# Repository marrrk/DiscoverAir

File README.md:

# DiscoverAir

A Datalogging HAT for the STM32F0 Discovery Board

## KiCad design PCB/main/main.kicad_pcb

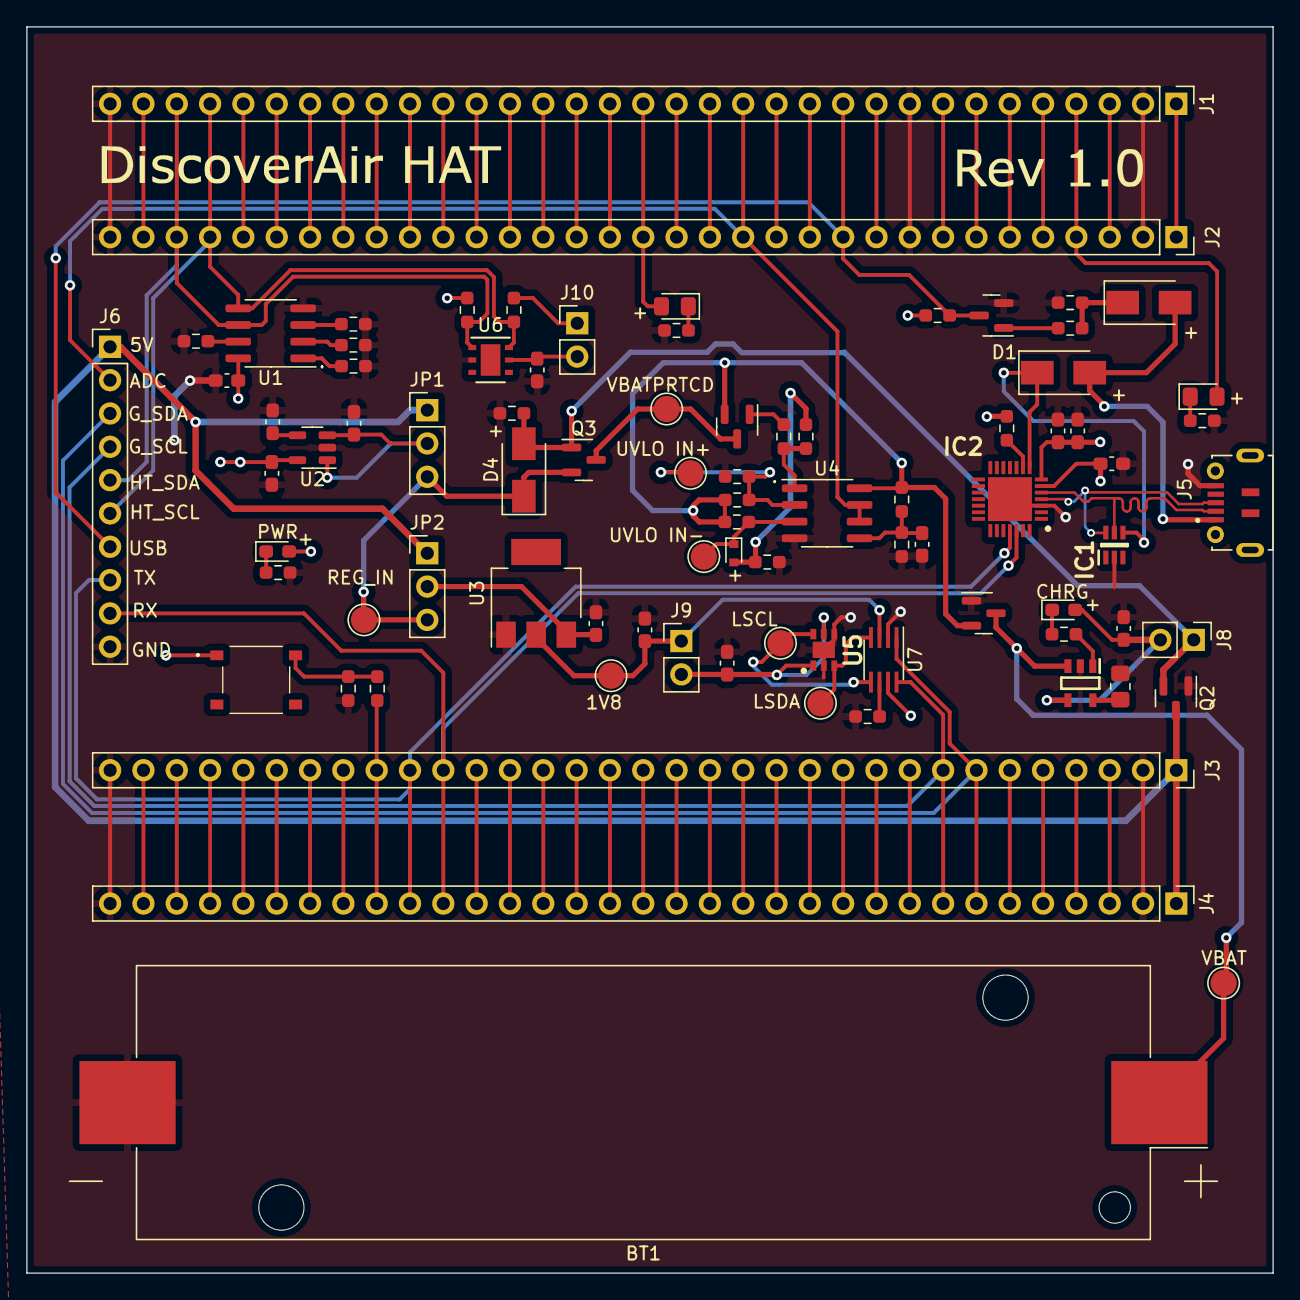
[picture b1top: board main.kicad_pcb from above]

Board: 2 copper layers, 95.0 x 95.0 mm, 84 parts (0 on the bottom side), 101 nets.

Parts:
BT1: Battery_Cell; BatteryHolder_Keystone_1042_1x18650
C1, C5, C6, C8, C9, C10, C11: 1uF; C_0603_1608Metric_Pad1.08x0.95mm_HandSolder
C2, C3, C4, C12, C13: 100nF; C_0603_1608Metric_Pad1.08x0.95mm_HandSolder
C7: 10nF; C_0603_1608Metric_Pad1.08x0.95mm_HandSolder
D1, D2, D4: D_Schottky; D_SMA
D3: CHRG; LED_0603_1608Metric_Pad1.05x0.95mm_HandSolder
D5: D_Zener; D_SOD-523
D6: PWR; LED_0603_1608Metric_Pad1.05x0.95mm_HandSolder
D7, D8: USER; LED_0805_2012Metric_Pad1.15x1.40mm_HandSolder
IC1: SMF05CT1G; SOT65P210X110-6N
IC2: CP2102-GMR; QFN50P500X500X100-29N-D
IC3: TP4054-42-SOT25-R; SOT95P280X100-5N
J1, J4: Conn_01x33_Female; PinHeader_1x33_P2.54mm_Vertical
J2, J3: Conn_01x33_Female; PinSocket_1x33_P2.54mm_Vertical
J5: USB_B_Micro; SHOUHAN_MICROXNJ
J6: Conn_01x10_Male; PinHeader_1x10_P2.54mm_Vertical
J8, J9, J10: Conn_01x02_Male; PinHeader_1x02_P2.54mm_Vertical
JP1, JP2: Jumper_3_Open; PinHeader_1x03_P2.54mm_Vertical
Q1: Q_NMOS_GSD; SOT-23
Q2, Q3, Q4, Q5: Q_PMOS_GSD; SOT-23
R1, R2, R3, R4, R5, R6, R7, R8, R10, R20, R22, R23: 4k7; R_0603_1608Metric_Pad0.98x0.95mm_HandSolder
R9: 510; R_0603_1608Metric_Pad0.98x0.95mm_HandSolder
R11: 5K1; R_0805_2012Metric_Pad1.20x1.40mm_HandSolder
R12, R19: 2.2M; R_0603_1608Metric_Pad0.98x0.95mm_HandSolder
R13, R15, R18: 1M; R_0603_1608Metric_Pad0.98x0.95mm_HandSolder
R14, R26: 300K; R_0603_1608Metric_Pad0.98x0.95mm_HandSolder
R16, R21, R24, R25, R27: 150; R_0603_1608Metric_Pad0.98x0.95mm_HandSolder
R17: 100; R_0603_1608Metric_Pad0.98x0.95mm_HandSolder
S1: TS-1187A-B-A-B; TS1187ABAB
TP2: 1V8; TestPoint_Pad_D2.0mm
TP4: UVLO_Out; TestPoint_Pad_D2.0mm
TP5: REG_IN; TestPoint_Pad_D2.0mm
TP6: VBAT; TestPoint_Pad_D2.0mm
TP7: UVLO V+; TestPoint_Pad_D2.0mm
TP8: UVLO V-; TestPoint_Pad_D2.0mm
TP9: GAS_SDA; TestPoint_Pad_D2.0mm
TP10: GAS_SCL; TestPoint_Pad_D2.0mm
U1: CAT24C256; SOIC-8_3.9x4.9mm_P1.27mm
U2: SGM2007-3.3XN5/TR; SOT-23-5
U3: AMS1117-1.8; SOT-223
U4: LM358; SOIC-8_3.9x4.9mm_P1.27mm
U5: SGP30-2.5k; SON80P245X245X90-7N
U6: HDC1080; Texas_PWSON-N6
U7: TXS0102DCT; SSOP-8_2.95x2.8mm_P0.65mm

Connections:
+1V8: C8.1, J9.1, TP2.1, U3.2 (VO), U7.3 (VCCA)
+3V0: C1.1, C2.1, C3.1, C4.1, C9.1, D6.2 (A), IC2.6 (VDD), IC2.7 (REGIN), J1.1, J2.1, J10.1, R3.1, R4.2, R22.2, R23.2, S1.A1 (COM_1), U1.8 (VCC), U2.5 (OUT), U7.7 (VCCB)
+5V: J3.1, J4.1, J6.1, JP1.1 (A), JP2.1 (A), Q2.3 (D)
/BOOT: J3.6, J4.6
/DN: IC1.5 (K_4), IC2.5 (D-), J5.2 (D-)
/DP: IC1.6 (K_5), IC2.4 (D+), J5.3 (D+)
/NRST: J1.10, J2.10
/PA0: J1.15, J2.15
/PA1: J1.16, J2.16
/PA2: D7.2 (A), J1.17, J2.17
/PA3: J1.18, J2.18
/PA4: J1.21, J2.21
/PA5: J1.22, J2.22
/PA6: J1.23, J2.23
/PA7: J1.24, J2.24
/PA8: J3.25, J4.25, R27.2
/PA9: IC2.25 (RXD), J3.24, J4.24, J6.8
/PA10: IC2.26 (TXD), J3.23, J4.23, J6.9
/PA11: J3.22, J4.22
/PA12: J3.21, J4.21
/PA13: J3.20, J4.20
/PA14: J3.17, J4.17
/PA15: J3.16, J4.16
/PB0: J1.27, J2.27
/PB1: J1.28, J2.28
/PB2: J1.29, J2.29
/PB3: J3.11, J4.11
/PB4: J3.10, J4.10
/PB5: J3.9, J4.9
/PB6: J3.8, J4.8, J6.4, U7.8 (B1)
/PB7: J3.7, J4.7, J6.3, U7.1 (B2)
/PB8: J3.4, J4.4
/PB9: J3.3, J4.3
/PB10: J1.30, J2.30, J6.6, R22.1, U1.5 (SDA), U6.6 (SCL)
/PB11: J1.31, J2.31, J6.5, R23.1, U1.6 (SCL), U6.1 (SDA)
/PB12: J1.32, J2.32
/PB13: J3.32, J4.32
/PB14: J3.31, J4.31
/PB15: J3.30, J4.30
/PC0: J1.11, J2.11, J6.7, Q1.3 (D), R3.2
/PC1: J1.12, J2.12
/PC2: J1.13, J2.13
/PC3: J1.14, J2.14, J6.2, U4.6 (-), U4.7
/PC4: J1.25, J2.25
/PC5: J1.26, J2.26
/PC6: J3.29, J4.29
/PC7: J3.28, J4.28
/PC8: J3.27, J4.27
/PC9: J3.26, J4.26
/PC10: J3.15, J4.15
/PC11: J3.14, J4.14
/PC12: J3.13, J4.13
/PC13: D8.2 (A), J1.4, J2.4
/PC14: J1.5, J2.5
/PC15: J1.6, J2.6
/PD2: J3.12, J4.12
/PF0: J1.7, J2.7
/PF1: J1.8, J2.8
/PF4: J1.19, J2.19
/PF5: J1.20, J2.20
/PF6: J3.19, J4.19
/PF7: J3.18, J4.18
/Power/Charger_In: D4.2 (A), J8.1, Q2.2 (S), Q3.1 (G), R10.2
/Power/REG_IN: D4.1 (K), JP1.3 (B), JP2.3 (B), Q3.2 (S), TP5.1
/Power/UVLO_IN: Q4.2 (S), Q5.2 (S), R12.1, R14.1, R16.1, U4.8 (V+)
/Power/VBAT: BT1.1 (+), IC3.3 (BAT), Q4.3 (D), TP6.1
/Power/VBAT_PRTCD: Q3.3 (D), Q5.3 (D), TP4.1
/VBAT: J1.3, J2.3
GND: BT1.2 (-), C1.2, C2.2, C3.2, C4.2, C5.2, C6.2, C7.1, C8.2, C9.2, C10.2, C11.2, C12.2, C13.2, IC1.2 (A), IC2.3 (GND), IC2.29 (TPAD), IC3.2 (GND), J1.2, J1.9, J1.33, J2.2, J2.9, J2.33, J3.2, J3.33, J4.2, J4.33, J5.5 (GND), J6.10, Q1.2 (S), Q2.1 (G), Q4.1 (G), R1.1, R5.1, R6.1, R7.1, R8.1, R10.1, R11.2, R13.2, R15.2, R17.2, R20.1, R21.2, R24.2, R25.2, R26.2, U1.4 (GND), U2.2 (GND), U3.1 (GND), U4.4 (V-), U5.2 (VSS), U5.4 (R), U5.7 (PAD), U6.2 (GND), U7.2 (GND)
unnamed: C5.1, JP1.2 (C), U2.1 (IN), U2.3 (EN)
unnamed: C6.1, JP2.2 (C), U3.3 (VI)
unnamed: C7.2, U2.4 (BP)
unnamed: C10.1, D3.2 (A), IC3.4 (VCC), J8.2
unnamed: C11.1, R12.2, R13.1, U4.5 (+)
unnamed: C12.1, J9.2, U5.1 (VDD), U5.5 (VDDH)
unnamed: C13.1, J10.2, U6.5 (VCC)
unnamed: D1.2 (A), D2.2 (A), J5.1 (VBUS)
unnamed: D2.1 (K), R1.2, R2.2
unnamed: D3.1 (K), R9.1
unnamed: D5.1 (K), R16.2, TP8.1, U4.3 (+)
unnamed: D5.2 (A), R17.1, R19.2
unnamed: D6.1 (K), R21.1
unnamed: D7.1 (K), R24.1
unnamed: D8.1 (K), R25.1
unnamed: IC2.9 (~RST), R4.1
unnamed: IC3.1 (~CHRG), R9.2
unnamed: IC3.5 (PROG), R11.1
unnamed: Q1.1 (G), R2.1
unnamed: Q5.1 (G), R18.1
unnamed: R5.2, U1.1 (A0)
unnamed: R6.2, U1.2 (A1)
unnamed: R7.2, U1.3 (A2)
unnamed: R8.2, U1.7 (WP)
unnamed: R14.2, R15.1, TP7.1, U4.2 (-)
unnamed: R18.2, R19.1, U4.1
unnamed: R20.2, U7.6 (OE)
unnamed: R26.1, R27.1, S1.B1 (COM_2)
unnamed: TP9.1, U5.3 (SDA), U7.4 (A2)
unnamed: TP10.1, U5.6 (SCL), U7.5 (A1)
VBUS: D1.1 (K), IC1.4 (K_3), IC2.8 (VBUS)
VDD: J3.5, J4.5

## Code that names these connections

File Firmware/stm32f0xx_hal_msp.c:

/* USER CODE BEGIN Header */
/**
  ******************************************************************************
  * @file         stm32f0xx_hal_msp.c
  * @brief        This file provides code for the MSP Initialization
  *               and de-Initialization codes.
  ******************************************************************************
  * @attention
  *
  * Copyright (c) 2022 STMicroelectronics.
  * All rights reserved.
  *
  * This software is licensed under terms that can be found in the LICENSE file
  * in the root directory of this software component.
  * If no LICENSE file comes with this software, it is provided AS-IS.
  *
  ******************************************************************************
  */
/* USER CODE END Header */

/* Includes ------------------------------------------------------------------*/
#include "main.h"
/* USER CODE BEGIN Includes */

/* USER CODE END Includes */

/* Private typedef -----------------------------------------------------------*/
/* USER CODE BEGIN TD */

/* USER CODE END TD */

/* Private define ------------------------------------------------------------*/
/* USER CODE BEGIN Define */

/* USER CODE END Define */

/* Private macro -------------------------------------------------------------*/
/* USER CODE BEGIN Macro */

/* USER CODE END Macro */

/* Private variables ---------------------------------------------------------*/
/* USER CODE BEGIN PV */

/* USER CODE END PV */

/* Private function prototypes -----------------------------------------------*/
/* USER CODE BEGIN PFP */

/* USER CODE END PFP */

/* External functions --------------------------------------------------------*/
/* USER CODE BEGIN ExternalFunctions */

/* USER CODE END ExternalFunctions */

/* USER CODE BEGIN 0 */

/* USER CODE END 0 */
/**
  * Initializes the Global MSP.
  */
void HAL_MspInit(void)
{
  /* USER CODE BEGIN MspInit 0 */

  /* USER CODE END MspInit 0 */

  __HAL_RCC_SYSCFG_CLK_ENABLE();
  __HAL_RCC_PWR_CLK_ENABLE();

  /* System interrupt init*/

  /* USER CODE BEGIN MspInit 1 */

  /* USER CODE END MspInit 1 */
}

/**
* @brief I2C MSP Initialization
* This function configures the hardware resources used in this example
* @param hi2c: I2C handle pointer
* @retval None
*/
void HAL_I2C_MspInit(I2C_HandleTypeDef* hi2c)
{
  GPIO_InitTypeDef GPIO_InitStruct = {0};
  if(hi2c->Instance==I2C1)
  {
  /* USER CODE BEGIN I2C1_MspInit 0 */

  /* USER CODE END I2C1_MspInit 0 */

    __HAL_RCC_GPIOB_CLK_ENABLE();
    /**I2C1 GPIO Configuration
    PB6     ------> I2C1_SCL
    PB7     ------> I2C1_SDA
    */
    GPIO_InitStruct.Pin = GPIO_PIN_6|GPIO_PIN_7;
    GPIO_InitStruct.Mode = GPIO_MODE_AF_OD;
    GPIO_InitStruct.Pull = GPIO_NOPULL;
    GPIO_InitStruct.Speed = GPIO_SPEED_FREQ_HIGH;
    GPIO_InitStruct.Alternate = GPIO_AF1_I2C1;
    HAL_GPIO_Init(GPIOB, &GPIO_InitStruct);

    /* Peripheral clock enable */
    __HAL_RCC_I2C1_CLK_ENABLE();
  /* USER CODE BEGIN I2C1_MspInit 1 */

  /* USER CODE END I2C1_MspInit 1 */
  }
  else if(hi2c->Instance==I2C2)
  {
  /* USER CODE BEGIN I2C2_MspInit 0 */

  /* USER CODE END I2C2_MspInit 0 */

    __HAL_RCC_GPIOB_CLK_ENABLE();
    /**I2C2 GPIO Configuration
    PB10     ------> I2C2_SCL
    PB11     ------> I2C2_SDA
    */
    GPIO_InitStruct.Pin = GPIO_PIN_10|GPIO_PIN_11;
    GPIO_InitStruct.Mode = GPIO_MODE_AF_OD;
    GPIO_InitStruct.Pull = GPIO_NOPULL;
    GPIO_InitStruct.Speed = GPIO_SPEED_FREQ_HIGH;
    GPIO_InitStruct.Alternate = GPIO_AF1_I2C2;
    HAL_GPIO_Init(GPIOB, &GPIO_InitStruct);

    /* Peripheral clock enable */
    __HAL_RCC_I2C2_CLK_ENABLE();
  /* USER CODE BEGIN I2C2_MspInit 1 */

  /* USER CODE END I2C2_MspInit 1 */
  }

}

/**
* @brief I2C MSP De-Initialization
* This function freeze the hardware resources used in this example
* @param hi2c: I2C handle pointer
* @retval None
*/
void HAL_I2C_MspDeInit(I2C_HandleTypeDef* hi2c)
{
  if(hi2c->Instance==I2C1)
  {
  /* USER CODE BEGIN I2C1_MspDeInit 0 */

  /* USER CODE END I2C1_MspDeInit 0 */
    /* Peripheral clock disable */
    __HAL_RCC_I2C1_CLK_DISABLE();

    /**I2C1 GPIO Configuration
    PB6     ------> I2C1_SCL
    PB7     ------> I2C1_SDA
    */
    HAL_GPIO_DeInit(GPIOB, GPIO_PIN_6);

    HAL_GPIO_DeInit(GPIOB, GPIO_PIN_7);

  /* USER CODE BEGIN I2C1_MspDeInit 1 */

  /* USER CODE END I2C1_MspDeInit 1 */
  }
  else if(hi2c->Instance==I2C2)
  {
  /* USER CODE BEGIN I2C2_MspDeInit 0 */

  /* USER CODE END I2C2_MspDeInit 0 */
    /* Peripheral clock disable */
    __HAL_RCC_I2C2_CLK_DISABLE();

    /**I2C2 GPIO Configuration
    PB10     ------> I2C2_SCL
    PB11     ------> I2C2_SDA
    */
    HAL_GPIO_DeInit(GPIOB, GPIO_PIN_10);

    HAL_GPIO_DeInit(GPIOB, GPIO_PIN_11);

  /* USER CODE BEGIN I2C2_MspDeInit 1 */

  /* USER CODE END I2C2_MspDeInit 1 */
  }

}

/**
* @brief UART MSP Initialization
* This function configures the hardware resources used in this example
* @param huart: UART handle pointer
* @retval None
*/
void HAL_UART_MspInit(UART_HandleTypeDef* huart)
{
  GPIO_InitTypeDef GPIO_InitStruct = {0};
  if(huart->Instance==USART2)
  {
  /* USER CODE BEGIN USART2_MspInit 0 */

  /* USER CODE END USART2_MspInit 0 */
    /* Peripheral clock enable */
    __HAL_RCC_USART2_CLK_ENABLE();

    __HAL_RCC_GPIOA_CLK_ENABLE();
    /**USART2 GPIO Configuration
    PA2     ------> USART2_TX
    PA3     ------> USART2_RX
    */
    GPIO_InitStruct.Pin = GPIO_PIN_2|GPIO_PIN_3;
    GPIO_InitStruct.Mode = GPIO_MODE_AF_PP;
    GPIO_InitStruct.Pull = GPIO_NOPULL;
    GPIO_InitStruct.Speed = GPIO_SPEED_FREQ_HIGH;
    GPIO_InitStruct.Alternate = GPIO_AF1_USART2;
    HAL_GPIO_Init(GPIOA, &GPIO_InitStruct);

  /* USER CODE BEGIN USART2_MspInit 1 */

  /* USER CODE END USART2_MspInit 1 */
  }

}

/**
* @brief UART MSP De-Initialization
* This function freeze the hardware resources used in this example
* @param huart: UART handle pointer
* @retval None
*/
void HAL_UART_MspDeInit(UART_HandleTypeDef* huart)
{
  if(huart->Instance==USART2)
  {
  /* USER CODE BEGIN USART2_MspDeInit 0 */

  /* USER CODE END USART2_MspDeInit 0 */
    /* Peripheral clock disable */
    __HAL_RCC_USART2_CLK_DISABLE();

    /**USART2 GPIO Configuration
    PA2     ------> USART2_TX
    PA3     ------> USART2_RX
    */
    HAL_GPIO_DeInit(GPIOA, GPIO_PIN_2|GPIO_PIN_3);

  /* USER CODE BEGIN USART2_MspDeInit 1 */

  /* USER CODE END USART2_MspDeInit 1 */
  }

}

/* USER CODE BEGIN 1 */

/* USER CODE END 1 */

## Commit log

2022-03-23 updated UVLO circuit
2022-03-26 added digital sensors
2022-03-27 added eeprom and some usb-uart connections
2022-03-28 added ESD protection and updated USB IC
2022-04-07 layout started
2022-04-08 started on routing
2022-04-11 ver 1 complete
2022-05-27 added image to README
2022-06-20 added firmware directory
2022-07-22 Create bbb
2022-07-22 Create ddd
2022-07-22 Create ffff
